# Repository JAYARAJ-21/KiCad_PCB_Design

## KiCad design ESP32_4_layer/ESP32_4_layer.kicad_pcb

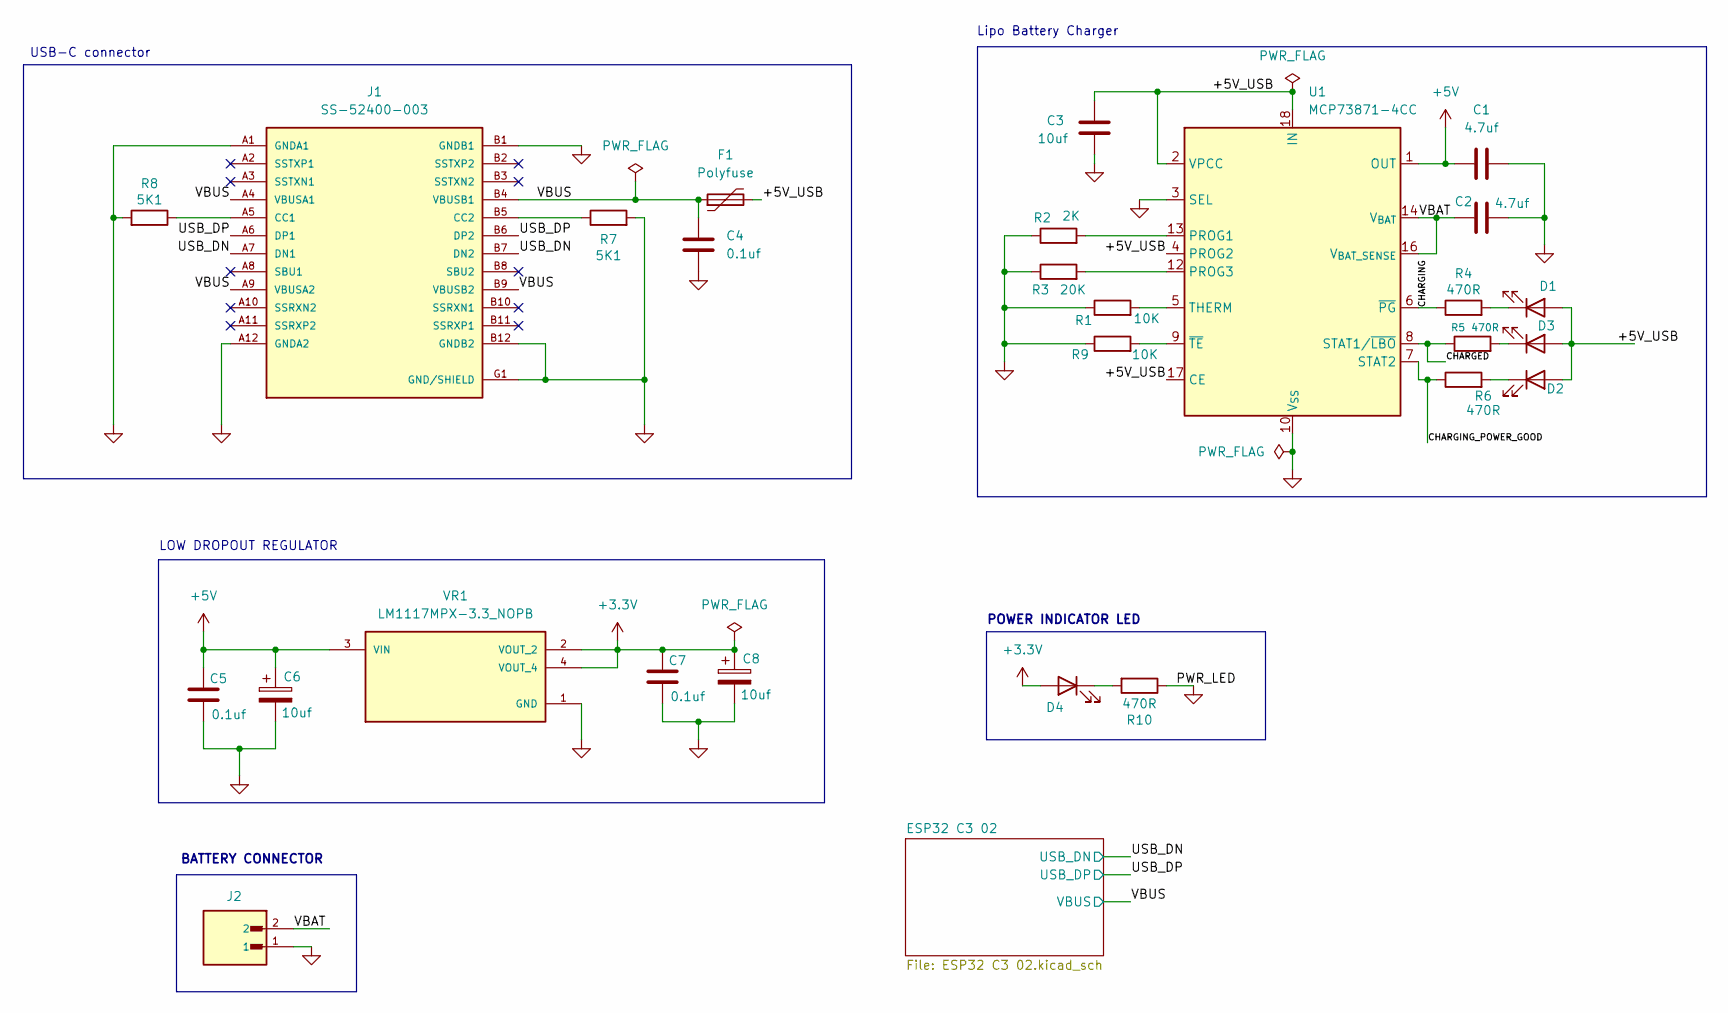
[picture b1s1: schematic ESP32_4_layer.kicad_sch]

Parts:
C1, C2: 4.7uf; C_0805_2012Metric
C3, C6: 10uf; C_0805_2012Metric
C4, C5, C7: 0.1uf; C_0805_2012Metric
C8: 10uf; T491A_Tantalum_Capacitor
D1: LED; Blue_Led_
D2, D4: LED; Red_Led
D3: LED; Green_led_LTST-C170GKT
F1: Polyfuse; Belfuse_FUSC3225X100N
J1: SS-52400-003; BELFUSE_SS-52400-003; PARTREV A0
J2: JST_S2B-PH-K-S_LF__SN_; PARTREV R0
R1, R9: 10K; R_0805_2012Metric
R2: 2K; R_0805_2012Metric
R3: 20K; R_0805_2012Metric
R4, R5, R6, R10: 470R; R_0805_2012Metric
R7, R8: 5K1; R_0805_2012Metric
U1: MCP73871-4CC; QFN-20-1EP_4x4mm_P0.5mm_EP2.5x2.5mm
VR1: LM1117MPX-3.3_NOPB; PARTREV O

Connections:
+3.3V: C7.1, C8.1, D4.2 (A), VR1.2 (VOUT_2), VR1.4 (VOUT_4); also elsewhere on the board
+5V: C1.1, C5.1, C6.1, U1.1 (OUT), U1.20 (OUT), VR1.3 (VIN)
/+5V_USB: C3.2, D1.2 (A), D2.2 (A), D3.2 (A), F1.2, U1.2 (VPCC), U1.4 (PROG2), U1.17 (CE), U1.18 (IN), U1.19 (IN)
/CHARGED: R5.1, U1.8 (STAT1/~LBO)
/CHARGING: R4.1, U1.6 (~PG)
/CHARGING_POWER_GOOD: R6.1, U1.7 (STAT2)
/USB_DN: J1.A7 (DN1), J1.B7 (DN2); also elsewhere on the board
/USB_DP: J1.A6 (DP1), J1.B6 (DP2); also elsewhere on the board
/VBAT: C2.1, J2.2, U1.14 (V_{BAT}), U1.15 (V_{BAT}), U1.16 (V_{BAT_SENSE})
/VBUS: C4.2, F1.1, J1.A4 (VBUSA1), J1.A9 (VBUSA2), J1.B4 (VBUSB1), J1.B9 (VBUSB2); also elsewhere on the board
GND: C1.2, C2.2, C3.1, C4.1, C5.2, C6.2, C7.2, C8.2, J1.A1 (GNDA1), J1.A12 (GNDA2), J1.B1 (GNDB1), J1.B12 (GNDB2), J1.G1 (GND/SHIELD), J1.G2 (GND/SHIELD), J1.G3 (GND/SHIELD), J1.G4 (GND/SHIELD), J1.S1 (GND/SHIELD), J1.S2 (GND/SHIELD), J1.S3 (GND/SHIELD), J1.S4 (GND/SHIELD), J2.1, R1.1, R2.1, R3.1, R7.2, R8.2, R9.1, R10.1, U1.3 (SEL), U1.10 (V_{SS}), U1.11 (V_{SS}), U1.21 (V_{SS}), VR1.1 (GND); also elsewhere on the board
unnamed: D1.1 (K), R4.2
unnamed: D2.1 (K), R6.2
unnamed: D3.1 (K), R5.2
unnamed: D4.1 (K), R10.2
unnamed: J1.A5 (CC1), R8.1
unnamed: J1.B5 (CC2), R7.1
unnamed: R2.2, U1.13 (PROG1)
unnamed: R3.2, U1.12 (PROG3)
unnamed: R1.2, U1.5 (THERM)
unnamed: R9.2, U1.9 (~TE)

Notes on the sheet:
Lipo Battery Charger
USB-C connector
LOW DROPOUT REGULATOR
BATTERY CONNECTOR
POWER INDICATOR LED

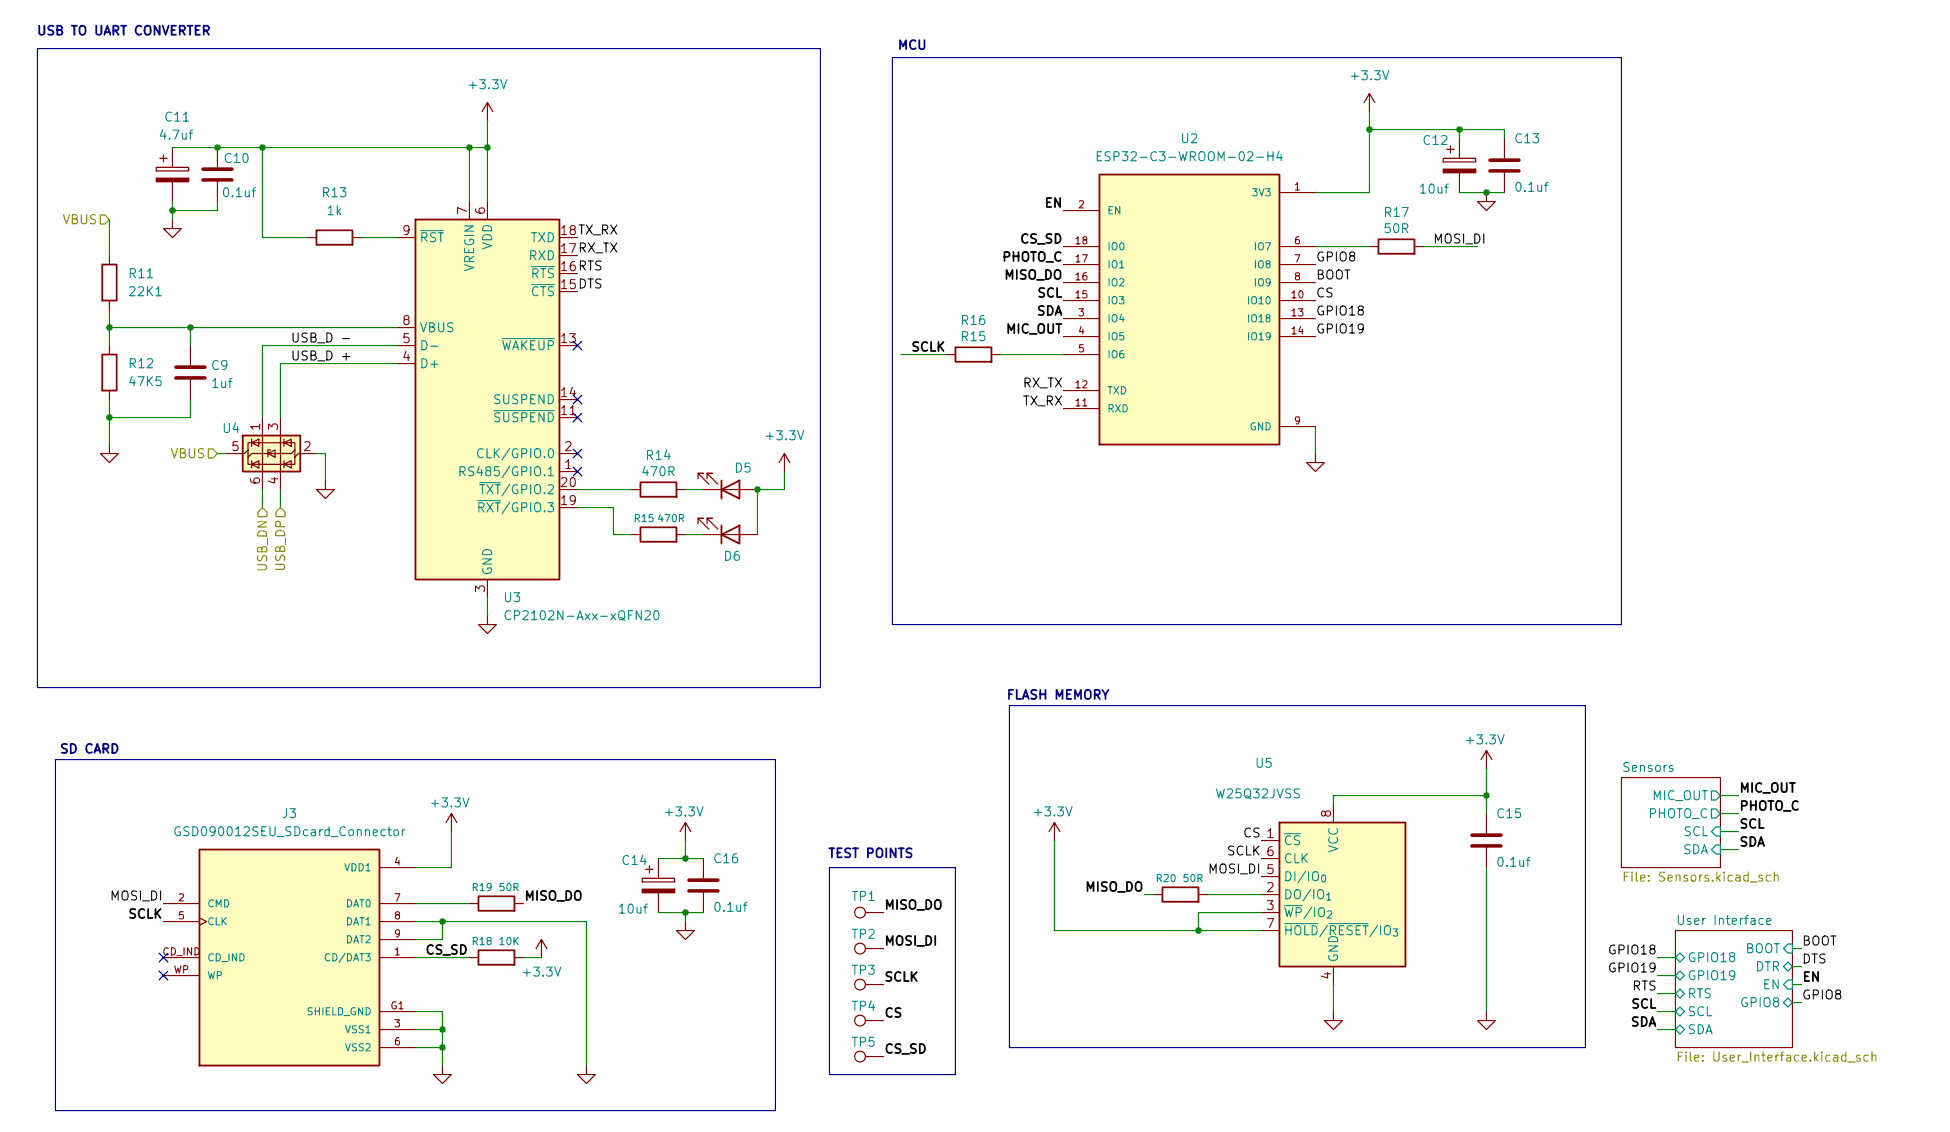
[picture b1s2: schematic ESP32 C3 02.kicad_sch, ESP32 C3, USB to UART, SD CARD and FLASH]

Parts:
C9: 1uf; C_0805_2012Metric
C10, C13, C15, C16: 0.1uf; C_0805_2012Metric
C11: 4.7uf; T491A_Tantalum_Capacitor
C12, C14: 10uf; T491A_Tantalum_Capacitor
D5: LED; Blue_Led_
D6: LED; Red_Led
J3: GSD090012SEU_SDcard_Connector; GSD090012SEU_SDCard_connector; PARTREV E
R11: 22K1; R_0805_2012Metric
R12: 47K5; R_0805_2012Metric
R13: 1k; R_0805_2012Metric
R14, R15: 470R; R_0805_2012Metric
R16: R15; R_0805_2012Metric
R17, R19, R20: 50R; R_0805_2012Metric
R18: 10K; R_0805_2012Metric
TP1, TP2, TP3, TP4, TP5: TestPoint; TestPoint_Pad_D1.0mm
U2: ESP32-C3-WROOM-02-H4
U3: CP2102N-Axx-xQFN20; QFN20_CP2102N_SIL
U4: USBLC6-2SC6; SOT-23-6
U5: W25Q32JVSS; SOIC-8_5.3x5.3mm_P1.27mm

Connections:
+3.3V: C10.1, C11.1, C12.1, C13.1, C14.1, C15.1, C16.1, D5.2 (A), D6.2 (A), J3.4 (VDD1), R13.1, R18.2, U2.1 (3V3), U3.6 (VDD), U3.7 (VREGIN), U5.3 (~WP/IO_{2}), U5.7 (~HOLD/~RESET/IO_{3}), U5.8 (VCC); also elsewhere on the board
/ESP32 C3 02/BOOT: U2.8 (IO9); also elsewhere on the board
/ESP32 C3 02/CS: TP4.1, U2.10 (IO10), U5.1 (~CS)
/ESP32 C3 02/CS_SD: J3.1 (CD/DAT3), R18.1, TP5.1, U2.18 (IO0)
/ESP32 C3 02/DTS: U3.15 (~CTS); also elsewhere on the board
/ESP32 C3 02/EN: U2.2 (EN); also elsewhere on the board
/ESP32 C3 02/GPIO8: U2.7 (IO8); also elsewhere on the board
/ESP32 C3 02/GPIO18: U2.13 (IO18); also elsewhere on the board
/ESP32 C3 02/GPIO19: U2.14 (IO19); also elsewhere on the board
/ESP32 C3 02/MIC_OUT: U2.4 (IO5); also elsewhere on the board
/ESP32 C3 02/MISO_DO: R19.2, R20.1, TP1.1, U2.16 (IO2)
/ESP32 C3 02/MOSI_DI: J3.2 (CMD), R17.2, TP2.1, U5.5 (DI/IO_{0})
/ESP32 C3 02/PHOTO_C: U2.17 (IO1); also elsewhere on the board
/ESP32 C3 02/RTS: U3.16 (~RTS); also elsewhere on the board
/ESP32 C3 02/RX_TX: U2.12 (TXD), U3.17 (RXD)
/ESP32 C3 02/SCL: U2.15 (IO3); also elsewhere on the board
/ESP32 C3 02/SCLK: J3.5 (CLK), R16.1, TP3.1, U5.6 (CLK)
/ESP32 C3 02/SDA: U2.3 (IO4); also elsewhere on the board
/ESP32 C3 02/TX_RX: U2.11 (RXD), U3.18 (TXD)
/ESP32 C3 02/USB_D +: U3.4 (D+), U4.3 (I/O2)
/ESP32 C3 02/USB_D -: U3.5 (D-), U4.1 (I/O1)
/USB_DN: U4.6 (I/O1); also elsewhere on the board
/USB_DP: U4.4 (I/O2); also elsewhere on the board
/VBUS: R11.1, U4.5 (VBUS); also elsewhere on the board
GND: C9.2, C10.2, C11.2, C12.2, C13.2, C14.2, C15.2, C16.2, J3.3 (VSS1), J3.6 (VSS2), J3.8 (DAT1), J3.9 (DAT2), J3.G1 (SHIELD_GND), J3.G2 (SHIELD_GND), J3.G3 (SHIELD_GND), J3.G4 (SHIELD_GND), R12.2, U2.9 (GND), U2.19 (GND), U2.20 (GND), U2.21 (GND), U2.22 (GND), U2.23 (GND), U2.24 (GND), U2.25 (GND), U2.26 (GND), U2.27 (GND), U2.28 (GND), U2.29 (GND), U2.30 (GND), U2.31 (GND), U2.32 (GND), U2.33 (GND), U2.34 (GND), U2.35 (GND), U2.36 (GND), U2.37 (GND), U2.38 (GND), U2.39 (GND), U3.3 (GND), U3.12 (GND), U3.21 (GND), U4.2 (GND), U5.4 (GND); also elsewhere on the board
unnamed: D5.1 (K), R14.2
unnamed: D6.1 (K), R15.2
unnamed: J3.7 (DAT0), R19.1
unnamed: R16.2, U2.5 (IO6)
unnamed: R17.1, U2.6 (IO7)
unnamed: C9.1, R11.2, R12.1, U3.8 (VBUS)
unnamed: R13.2, U3.9 (~RST)
unnamed: R15.1, U3.19 (~RXT/GPIO.3)
unnamed: R14.1, U3.20 (~TXT/GPIO.2)
unnamed: R20.2, U5.2 (DO/IO_{1})

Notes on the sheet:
MCU
FLASH MEMORY
SD CARD
TEST POINTS
USB TO UART CONVERTER

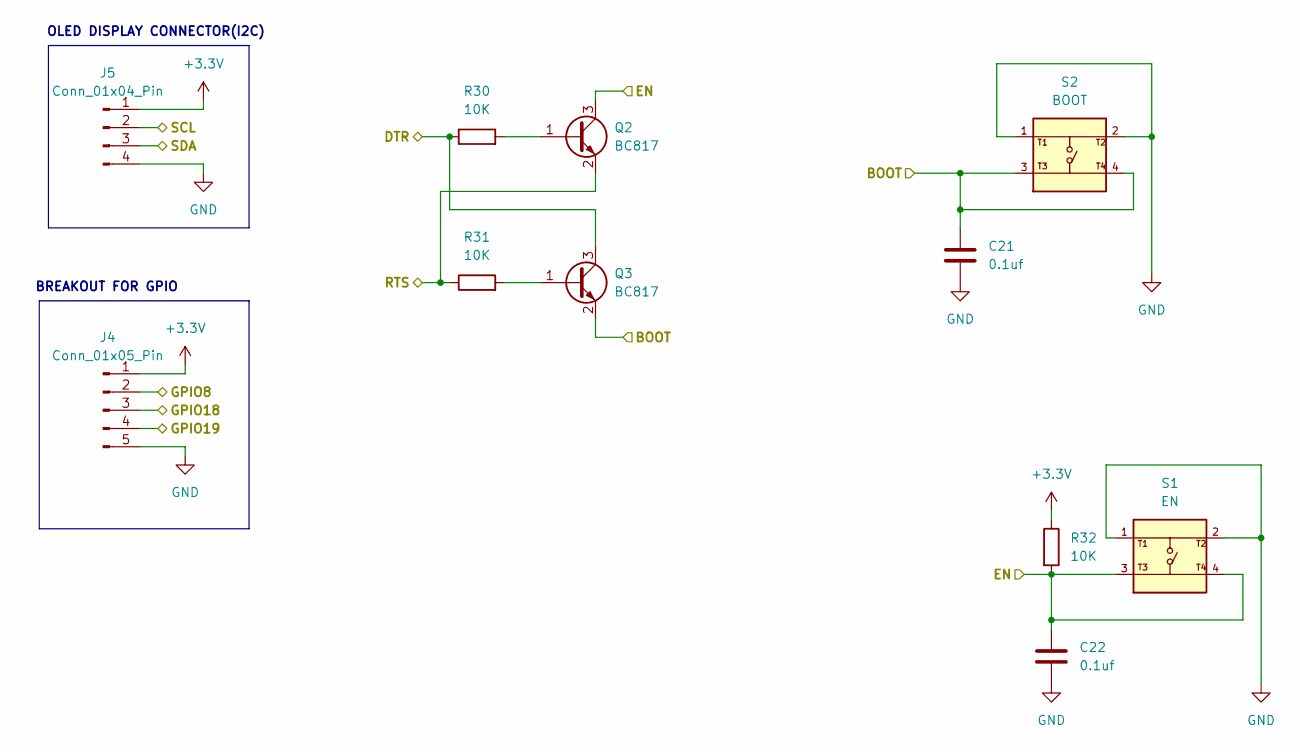
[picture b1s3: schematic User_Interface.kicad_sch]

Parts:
C21, C22: 0.1uf; C_0805_2012Metric
J4: Conn_01x05_Pin; PinHeader_1x05_P2.54mm_Vertical
J5: Conn_01x04_Pin; PinHeader_1x04_P2.54mm_Vertical
Q2, Q3: BC817; SOT-23
R30, R31, R32: 10K; R_0805_2012Metric
S1: EN; SW_USLPT2819DT2TR; PARTREV P
S2: BOOT; SW_USLPT2819DT2TR; PARTREV P

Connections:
+3.3V: J4.1, J5.1, R32.1; also elsewhere on the board
/ESP32 C3 02/BOOT: C21.1, Q3.2 (E), S2.3, S2.4; also elsewhere on the board
/ESP32 C3 02/DTS: Q3.3 (C), R30.1; also elsewhere on the board
/ESP32 C3 02/EN: C22.1, Q2.3 (C), R32.2, S1.3, S1.4; also elsewhere on the board
/ESP32 C3 02/GPIO8: J4.2; also elsewhere on the board
/ESP32 C3 02/GPIO18: J4.3; also elsewhere on the board
/ESP32 C3 02/GPIO19: J4.4; also elsewhere on the board
/ESP32 C3 02/RTS: Q2.2 (E), R31.1; also elsewhere on the board
/ESP32 C3 02/SCL: J5.2; also elsewhere on the board
/ESP32 C3 02/SDA: J5.3; also elsewhere on the board
GND: C21.2, C22.2, J4.5, J5.4, S1.1, S1.2, S2.1, S2.2; also elsewhere on the board
unnamed: Q2.1 (B), R30.2
unnamed: Q3.1 (B), R31.2

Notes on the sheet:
BREAKOUT FOR GPIO
OLED DISPLAY CONNECTOR(I2C)

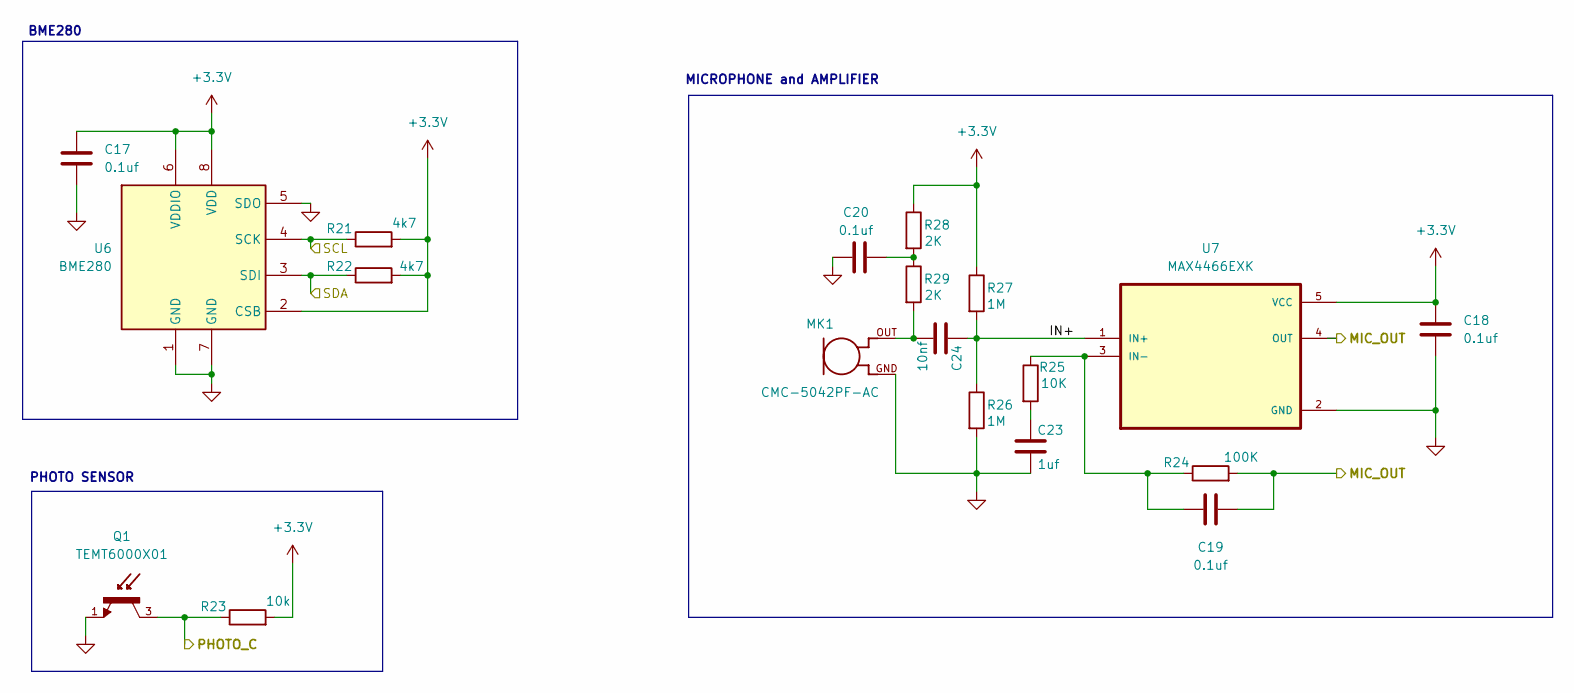
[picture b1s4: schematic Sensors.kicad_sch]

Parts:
C17, C18, C19, C20: 0.1uf; C_0805_2012Metric
C23: 1uf; C_0805_2012Metric
C24: 10nf; C_0805_2012Metric
MK1: CMC-5042PF-AC; CUI_CMC-5042PF-AC
Q1: TEMT6000X01; PARTREV 1.9
R21, R22: 4k7; R_0805_2012Metric
R23: 10k; R_0805_2012Metric
R24: 100K; R_0805_2012Metric
R25: 10K; R_0805_2012Metric
R26, R27: 1M; R_0805_2012Metric
R28, R29: 2K; R_0805_2012Metric
U6: BME280; Bosch_LGA-8_2.5x2.5mm_P0.65mm_ClockwisePinNumbering
U7: MAX4466EXK; MAX4466EXX

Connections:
+3.3V: C17.1, C18.1, R21.2, R22.2, R23.2, R27.1, R28.1, U6.2 (CSB), U6.6 (VDDIO), U6.8 (VDD), U7.5 (VCC); also elsewhere on the board
/ESP32 C3 02/MIC_OUT: C19.2, R24.2, U7.4 (OUT); also elsewhere on the board
/ESP32 C3 02/PHOTO_C: Q1.3, R23.1; also elsewhere on the board
/ESP32 C3 02/SCL: R21.1, U6.4 (SCK); also elsewhere on the board
/ESP32 C3 02/SDA: R22.1, U6.3 (SDI); also elsewhere on the board
/ESP32 C3 02/Sensors/IN+: C24.2, R26.1, R27.2, U7.1 (IN+)
GND: C17.2, C18.2, C20.1, C23.1, MK1.GND, Q1.1, R26.2, U6.1 (GND), U6.5 (SDO), U6.7 (GND), U7.2 (GND); also elsewhere on the board
unnamed: C20.2, R28.2, R29.1
unnamed: C23.2, R25.2
unnamed: C24.1, MK1.OUT, R29.2
unnamed: C19.1, R24.1, R25.1, U7.3 (IN-)

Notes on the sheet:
BME280
MICROPHONE and AMPLIFIER
PHOTO SENSOR

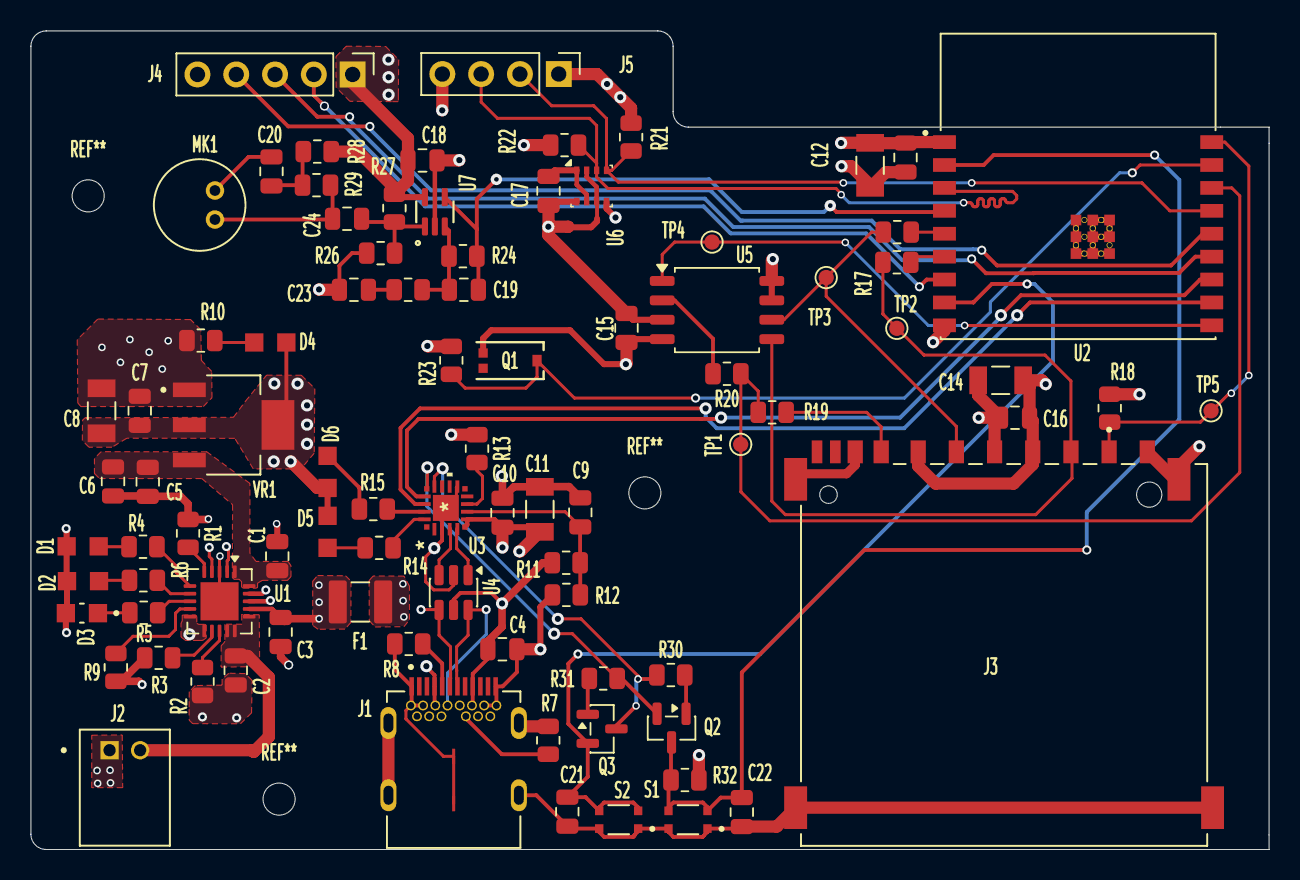
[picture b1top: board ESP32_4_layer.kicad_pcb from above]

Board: 4 copper layers, 81.1 x 53.6 mm, 87 parts (0 on the bottom side), 58 nets.

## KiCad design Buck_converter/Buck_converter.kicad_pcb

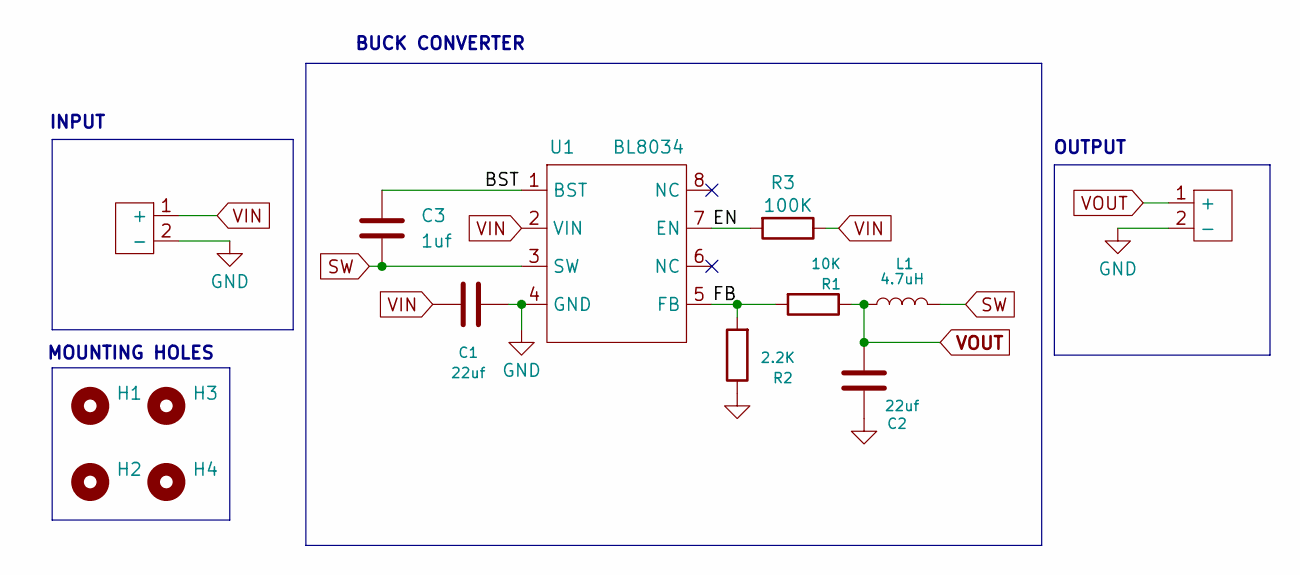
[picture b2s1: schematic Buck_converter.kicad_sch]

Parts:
C1, C2: 22uf; C_1206_3216Metric_Pad1.33x1.80mm_HandSolder
C3: 1uf; C_0603_1608Metric_Pad1.08x0.95mm_HandSolder
H1, H2, H3, H4: MountingHole; ToolingHole_1.152mm
J1, J2: pad
L1: 4.7uH; IND_NRS6045T101MMGKV
R1: 10K; R_0603_1608Metric_Pad0.98x0.95mm_HandSolder
R2: 2.2K; R_0603_1608Metric_Pad0.98x0.95mm_HandSolder
R3: 100K; R_0603_1608Metric_Pad0.98x0.95mm_HandSolder
U1: BL8034; bl8034_ESP08

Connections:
/BST: C3.1, U1.1 (BST)
/EN: R3.2, U1.7 (EN)
/FB: R1.2, R2.2, U1.5 (FB)
GND: C1.2, C2.1, J1.2 (-), J2.2 (-), R2.1, U1.4 (GND)
SW: C3.2, L1.2, U1.3 (SW)
VIN: C1.1, J2.1 (+), R3.1, U1.2 (VIN)
VOUT: C2.2, J1.1 (+), L1.1, R1.1

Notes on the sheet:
OUTPUT
BUCK CONVERTER
MOUNTING HOLES
INPUT

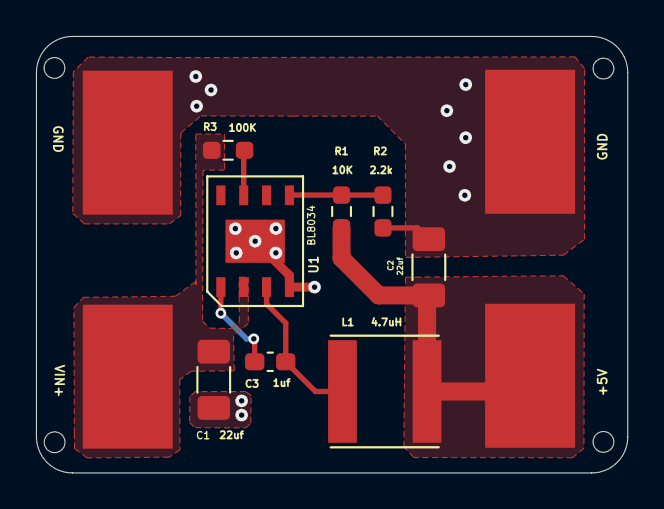
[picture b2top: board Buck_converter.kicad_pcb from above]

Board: 2 copper layers, 32.9 x 24.2 mm, 14 parts (0 on the bottom side), 7 nets.
